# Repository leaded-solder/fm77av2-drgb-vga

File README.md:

# Fujitsu FM77AV Digital RGB to VGA adapter

# Tested on
 - FM77AV-2

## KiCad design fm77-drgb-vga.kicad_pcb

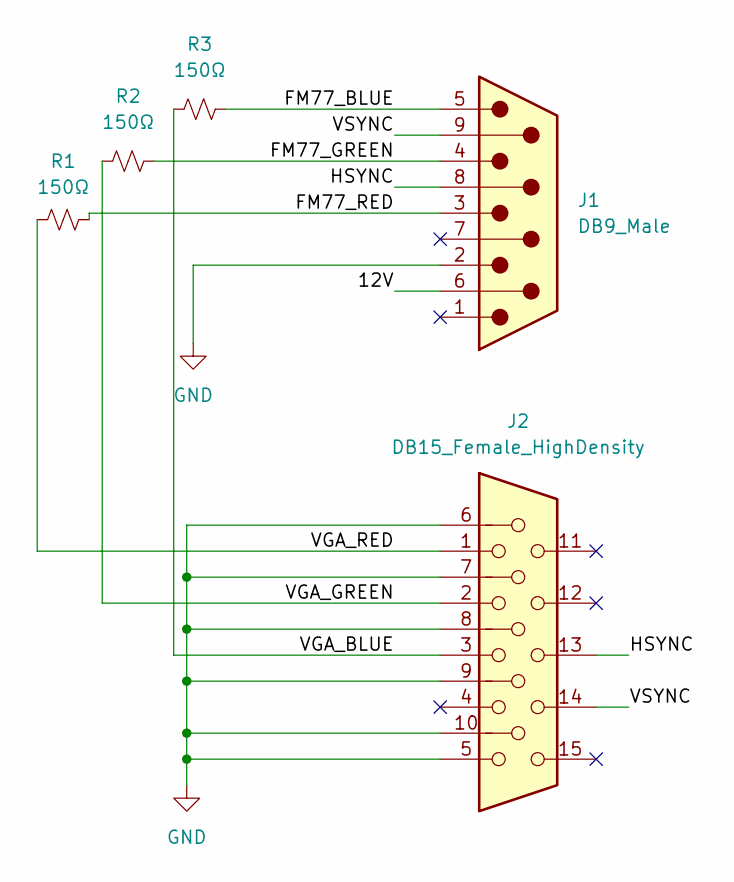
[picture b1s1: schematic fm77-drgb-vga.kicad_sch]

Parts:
J1: DB9_Male; A-DS 09 A-KG-T2S
J2: DB15_Female_HighDensity; FIXED-1-1734530-1
R1, R2, R3: 150Ω; R_Axial_DIN0207_L6.3mm_D2.5mm_P10.16mm_Horizontal

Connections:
/12V: J1.6
/FM77_BLUE: J1.5, R3.2
/FM77_GREEN: J1.4, R2.2
/FM77_RED: J1.3, R1.2
/HSYNC: J1.8, J2.13
/VGA_BLUE: J2.3, R3.1
/VGA_GREEN: J2.2, R2.1
/VGA_RED: J2.1, R1.1
/VSYNC: J1.9, J2.14
GND: J1.2, J2.5, J2.6, J2.7, J2.8, J2.9, J2.10

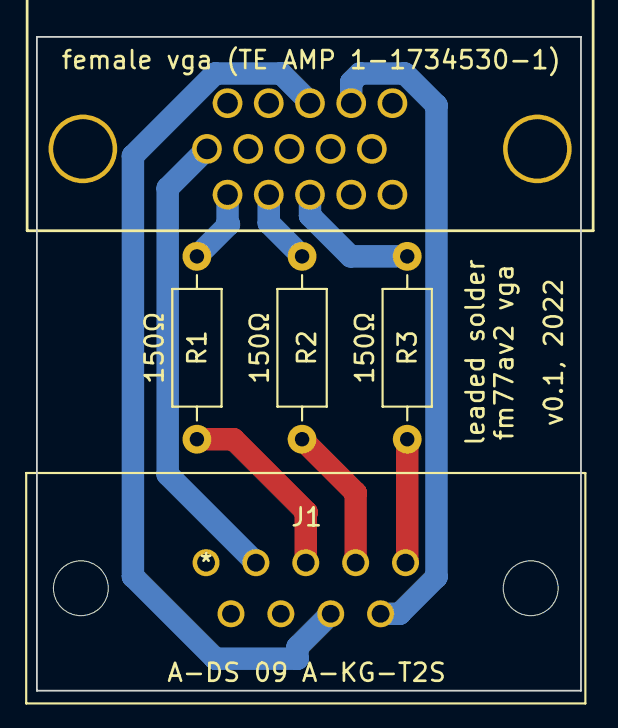
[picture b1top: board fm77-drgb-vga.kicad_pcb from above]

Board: 2 copper layers, 30.2 x 36.3 mm, 5 parts (0 on the bottom side), 9 nets.

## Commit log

2022-04-24 Initial commit, working adapter

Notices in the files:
parts and their libraries:
Copyright 2016 Accelerated Designs. All rights reserved.
